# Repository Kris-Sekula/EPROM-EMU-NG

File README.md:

# EPROM-EMU-NG
EPROM Emulator Project with Arduino Nano, read more on [https://MyGeekyHobby.com](https://mygeekyhobby.com/2020/07/05/eprom-emulator/)

I have assembled devices and kits listed on [eBay](https://www.ebay.com/usr/avr4sale)

As people start building those, I encourage everyone to help creating updated firmware, software and collaborate here, report Issues if needed or contact me directly.

I get my PCBs from:

If you found this helpful and you like the work I do, why not buy me a coffe, thanks ! :)

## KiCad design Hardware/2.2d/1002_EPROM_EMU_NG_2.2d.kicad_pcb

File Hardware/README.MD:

###### Jul-9-2022

As of hardware version 1.9d and 2.2d support for a cheaper 28 pin probe has been added to the PCB, so depending on the type of probe you end up using, connector J1 has to be soldered in accordingly, see the picture below:

###### Feb-6-2022

At this point there are two differnt hardware version of the emulator, one using 2x 32kb SRAMs and the other using a single 128kb SRAM (64k usable). Firmware and software is exaclty the same for both.

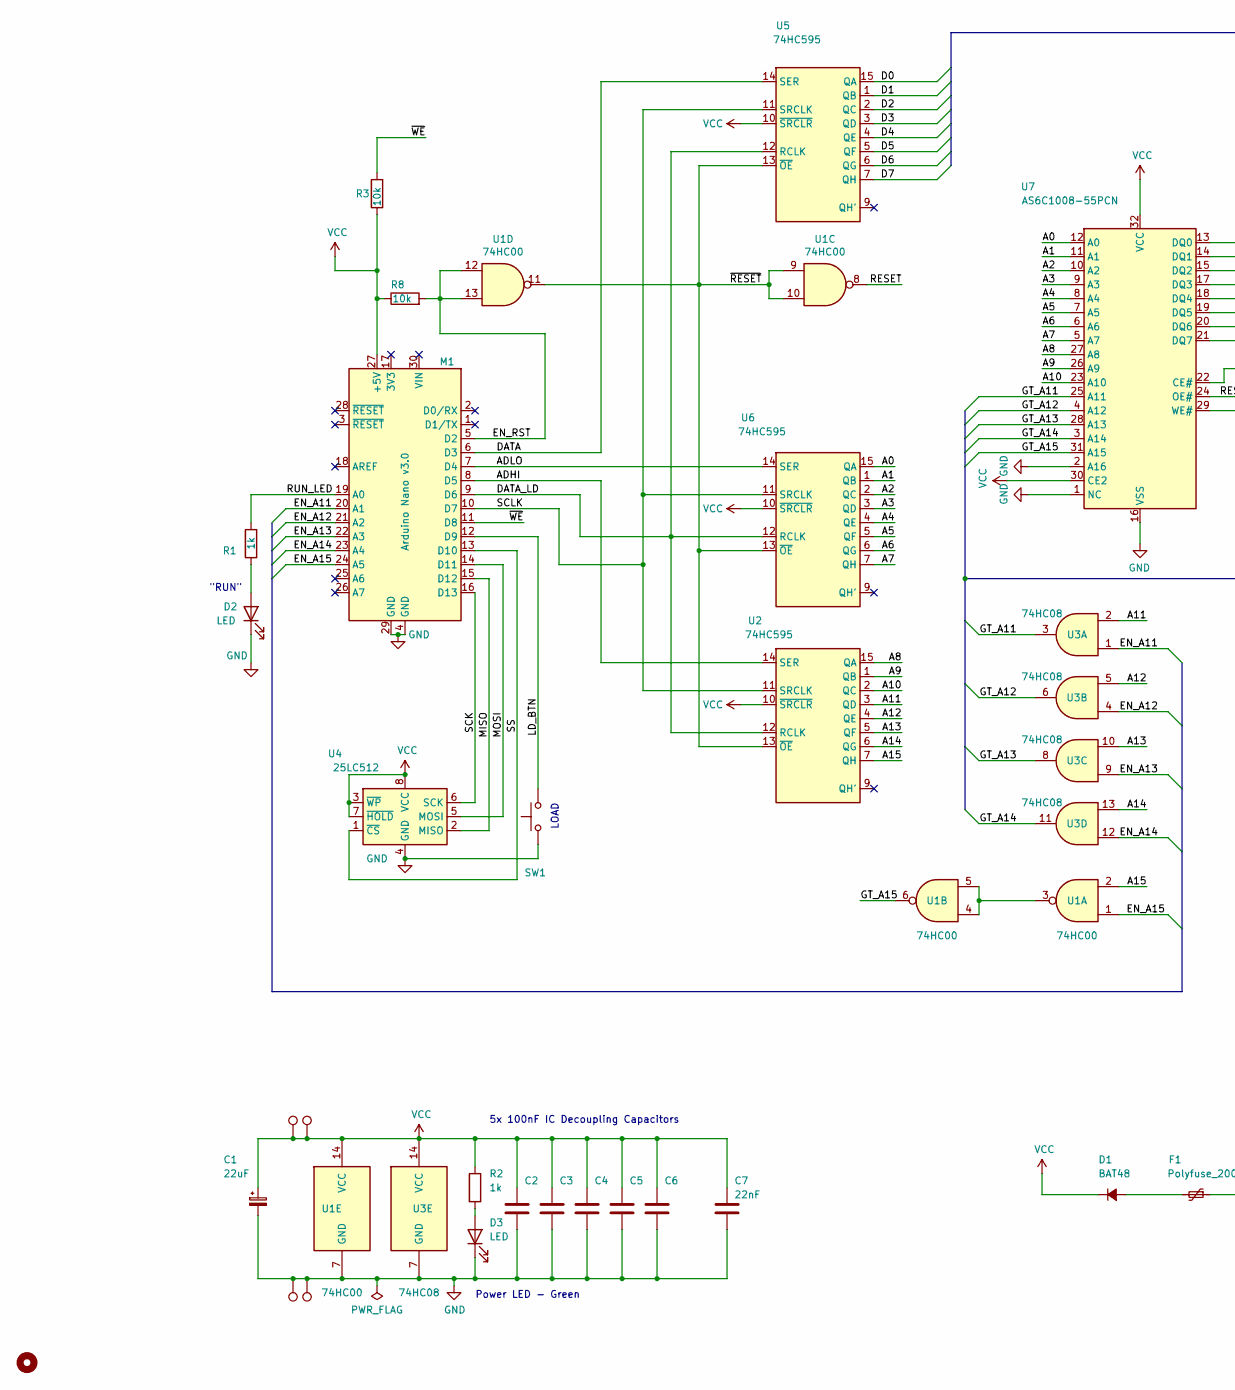
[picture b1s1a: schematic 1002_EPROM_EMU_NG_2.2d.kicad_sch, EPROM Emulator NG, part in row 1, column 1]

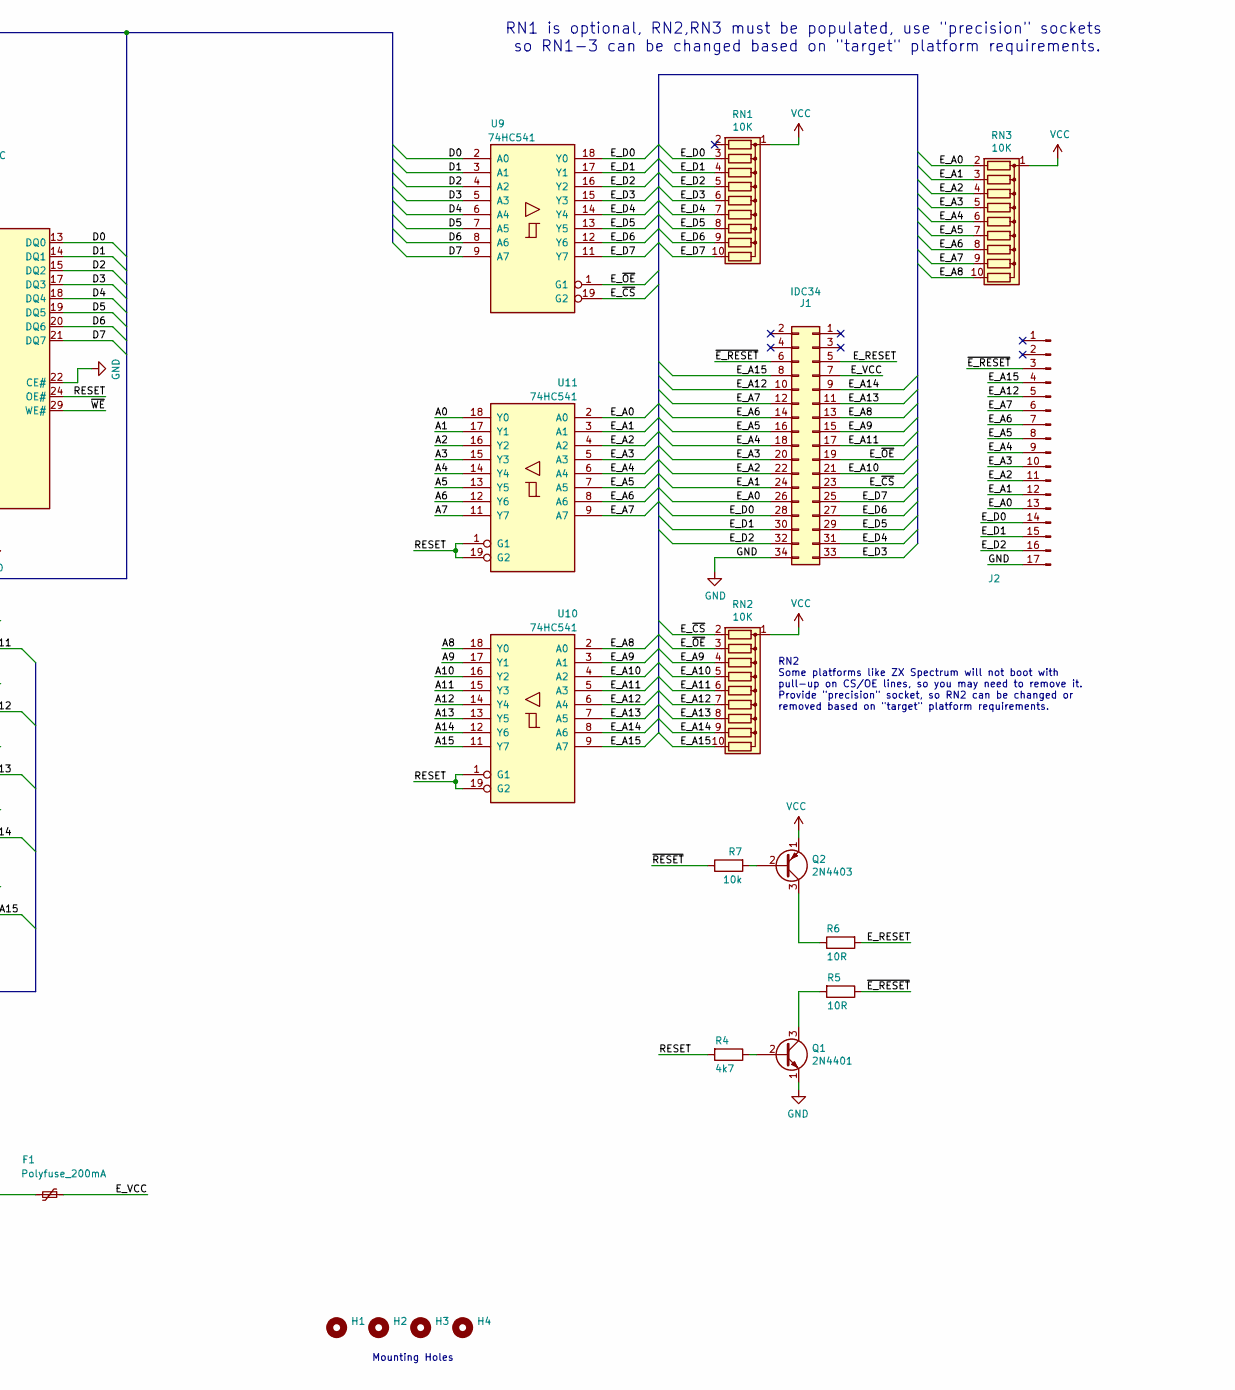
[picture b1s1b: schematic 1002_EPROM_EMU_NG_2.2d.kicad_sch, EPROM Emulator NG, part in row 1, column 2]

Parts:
C1: 22uF; CP_Radial_D6.3mm_P2.50mm
C2, C3, C4, C5, C6: 100nF; C_Disc_D4.7mm_W2.5mm_P5.00mm
C7: 22nF; C_Disc_D4.7mm_W2.5mm_P5.00mm
D1: BAT48; D_DO-35_SOD27_P7.62mm_Horizontal
D2, D3: LED; LED_D3.0mm
F1: Polyfuse_200mA; C_Disc_D10.0mm_W2.5mm_P5.00mm
H1, H2, H3, H4: MountingHole; MountingHole_2.2mm_M2
H5: MountingHole; OSHW-Logo2_9.8x8mm_SilkScreen
J1: IDC34; IDC-Header_2x17_P2.54mm_Horizontal_Lock
J2: Conn_01x17_Male; PinHeader_1x17_P2.54mm_Vertical
M1: Arduino Nano v3.0; Arduino_Nano
Q1: 2N4401; TO-92_Inline_Wide
Q2: 2N4403; TO-92_Inline_Wide
R1, R2: 1k; R_Axial_DIN0204_L3.6mm_D1.6mm_P7.62mm_Horizontal
R3, R7, R8: 10k; R_Axial_DIN0204_L3.6mm_D1.6mm_P7.62mm_Horizontal
R4: 4k7; R_Axial_DIN0204_L3.6mm_D1.6mm_P7.62mm_Horizontal
R5, R6: 10R; R_Axial_DIN0204_L3.6mm_D1.6mm_P7.62mm_Horizontal
RN1, RN2, RN3: 10K; R_Array_SIP10
SW1: SW_Push; SW_PUSH_6mm
TP1, TP4: VCC; TestPoint_THTPad_D1.5mm_Drill0.7mm
TP2, TP3: GND; TestPoint_THTPad_D1.5mm_Drill0.7mm
U1: 74HC00; DIP-14_W7.62mm_Socket
U2, U5, U6: 74HC595; DIP-16_W7.62mm_Socket
U3: 74HC08; DIP-14_W7.62mm_Socket
U4: 25LC512; DIP-8_W7.62mm_Socket
U7: AS6C1008-55PCN; DIP-32_W15.24mm_Socket
U9, U10, U11: 74HC541; DIP-20_W7.62mm_Socket

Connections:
/A0: U6.15 (QA), U7.12 (A0), U11.18 (Y0)
/A1: U6.1 (QB), U7.11 (A1), U11.17 (Y1)
/A2: U6.2 (QC), U7.10 (A2), U11.16 (Y2)
/A3: U6.3 (QD), U7.9 (A3), U11.15 (Y3)
/A4: U6.4 (QE), U7.8 (A4), U11.14 (Y4)
/A5: U6.5 (QF), U7.7 (A5), U11.13 (Y5)
/A6: U6.6 (QG), U7.6 (A6), U11.12 (Y6)
/A7: U6.7 (QH), U7.5 (A7), U11.11 (Y7)
/A8: U2.15 (QA), U7.27 (A8), U10.18 (Y0)
/A9: U2.1 (QB), U7.26 (A9), U10.17 (Y1)
/A10: U2.2 (QC), U7.23 (A10), U10.16 (Y2)
/A11: U2.3 (QD), U3.2, U10.15 (Y3)
/A12: U2.4 (QE), U3.5, U10.14 (Y4)
/A13: U2.5 (QF), U3.10, U10.13 (Y5)
/A14: U2.6 (QG), U3.13, U10.12 (Y6)
/A15: U1.2, U2.7 (QH), U10.11 (Y7)
/ADHI: M1.8 (D5), U2.14 (SER)
/ADLO: M1.7 (D4), U6.14 (SER)
/D0: U5.15 (QA), U7.13 (DQ0), U9.2 (A0)
/D1: U5.1 (QB), U7.14 (DQ1), U9.3 (A1)
/D2: U5.2 (QC), U7.15 (DQ2), U9.4 (A2)
/D3: U5.3 (QD), U7.17 (DQ3), U9.5 (A3)
/D4: U5.4 (QE), U7.18 (DQ4), U9.6 (A4)
/D5: U5.5 (QF), U7.19 (DQ5), U9.7 (A5)
/D6: U5.6 (QG), U7.20 (DQ6), U9.8 (A6)
/D7: U5.7 (QH), U7.21 (DQ7), U9.9 (A7)
/DATA: M1.6 (D3), U5.14 (SER)
/DATA_LD: M1.9 (D6), U2.12 (RCLK), U5.12 (RCLK), U6.12 (RCLK)
/EN_A11: M1.20 (A1), U3.1
/EN_A12: M1.21 (A2), U3.4
/EN_A13: M1.22 (A3), U3.9
/EN_A14: M1.23 (A4), U3.12
/EN_A15: M1.24 (A5), U1.1
/EN_RST: M1.5 (D2), R8.2, U1.12, U1.13
/E_A0: J1.26, J2.13, RN3.2 (R1), U11.2 (A0)
/E_A1: J1.24, J2.12, RN3.3 (R2), U11.3 (A1)
/E_A2: J1.22, J2.11, RN3.4 (R3), U11.4 (A2)
/E_A3: J1.20, J2.10, RN3.5 (R4), U11.5 (A3)
/E_A4: J1.18, J2.9, RN3.6 (R5), U11.6 (A4)
/E_A5: J1.16, J2.8, RN3.7 (R6), U11.7 (A5)
/E_A6: J1.14, J2.7, RN3.8 (R7), U11.8 (A6)
/E_A7: J1.12, J2.6, RN3.9 (R8), U11.9 (A7)
/E_A8: J1.13, RN3.10 (R9), U10.2 (A0)
/E_A9: J1.15, RN2.4 (R3), U10.3 (A1)
/E_A10: J1.21, RN2.5 (R4), U10.4 (A2)
/E_A11: J1.17, RN2.6 (R5), U10.5 (A3)
/E_A12: J1.10, J2.5, RN2.7 (R6), U10.6 (A4)
/E_A13: J1.11, RN2.8 (R7), U10.7 (A5)
/E_A14: J1.9, RN2.9 (R8), U10.8 (A6)
/E_A15: J1.8, J2.4, RN2.10 (R9), U10.9 (A7)
/E_D0: J1.28, J2.14, RN1.3 (R2), U9.18 (Y0)
/E_D1: J1.30, J2.15, RN1.4 (R3), U9.17 (Y1)
/E_D2: J1.32, J2.16, RN1.5 (R4), U9.16 (Y2)
/E_D3: J1.33, RN1.6 (R5), U9.15 (Y3)
/E_D4: J1.31, RN1.7 (R6), U9.14 (Y4)
/E_D5: J1.29, RN1.8 (R7), U9.13 (Y5)
/E_D6: J1.27, RN1.9 (R8), U9.12 (Y6)
/E_D7: J1.25, RN1.10 (R9), U9.11 (Y7)
/E_RESET: J1.5, R6.2
/E_VCC: F1.1, J1.7
/E_~CS: J1.23, RN2.2 (R1), U9.19 (G2)
/E_~OE: J1.19, RN2.3 (R2), U9.1 (G1)
/GT_A11: U3.3, U7.25 (A11)
/GT_A12: U3.6, U7.4 (A12)
/GT_A13: U3.8, U7.28 (A13)
/GT_A14: U3.11, U7.3 (A14)
/GT_A15: U1.6, U7.31 (A15)
/LD_BTN: M1.12 (D9), SW1.2
/MISO: M1.15 (D12), U4.2 (MISO)
/MOSI: M1.14 (D11), U4.5 (MOSI)
/RESET: R4.2, U1.8, U7.24 (OE#), U10.1 (G1), U10.19 (G2), U11.1 (G1), U11.19 (G2)
/RUN_LED: M1.19 (A0), R1.2
/SCK: M1.16 (D13), U4.6 (SCK)
/SCLK: M1.10 (D7), U2.11 (SRCLK), U5.11 (SRCLK), U6.11 (SRCLK)
/SS: M1.13 (D10), U4.1 (~CS)
/~E_RESET: J1.6, J2.3, R5.1
/~RESET: R7.1, U1.9, U1.10, U1.11, U2.13 (~OE), U5.13 (~OE), U6.13 (~OE)
/~WE: M1.11 (D8), R3.2, U7.29 (WE#)
GND: C1.2, C2.2, C3.2, C4.2, C5.2, C6.2, C7.2, D2.1 (K), D3.1 (K), J1.34, J2.17, M1.4 (GND), M1.29 (GND), Q1.1 (E), SW1.1, TP2.1, TP3.1, U1.7 (GND), U2.8 (GND), U3.7 (GND), U4.4 (GND), U5.8 (GND), U6.8 (GND), U7.1 (NC), U7.2 (A16), U7.16 (VSS), U7.22 (CE#), U9.10 (GND), U10.10 (GND), U11.10 (GND)
unnamed: D1.2 (A), F1.2
unnamed: D2.2 (A), R1.1
unnamed: D3.2 (A), R2.2
unnamed: Q1.2 (B), R4.1
unnamed: Q1.3 (C), R5.2
unnamed: Q2.2 (B), R7.2
unnamed: Q2.3 (C), R6.1
unnamed: U1.3, U1.4, U1.5
VCC: C1.1, C2.1, C3.1, C4.1, C5.1, C6.1, C7.1, D1.1 (K), M1.27 (+5V), Q2.1 (E), R2.1, R3.1, R8.1, RN1.1 (common), RN2.1 (common), RN3.1 (common), TP1.1, TP4.1, U1.14 (VCC), U2.10 (~SRCLR), U2.16 (VCC), U3.14 (VCC), U4.3 (~WP), U4.7 (~HOLD), U4.8 (VCC), U5.10 (~SRCLR), U5.16 (VCC), U6.10 (~SRCLR), U6.16 (VCC), U7.30 (CE2), U7.32 (VCC), U9.20 (VCC), U10.20 (VCC), U11.20 (VCC)

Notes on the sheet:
RN2 Some platforms like ZX Spectrum will not boot with pull-up on CS/OE lines, so you may need to remove it. Provide "precision" socket, so RN2 can be changed or removed based on "target" platform requirements.
"RUN"
Power LED - Green
LOAD
RN1 is optional, RN2,RN3 must be populated, use "precision" sockets so RN1-3 can be changed based on "target" platform requirements.
5x 100nF IC Decoupling Capacitors
Mounting Holes

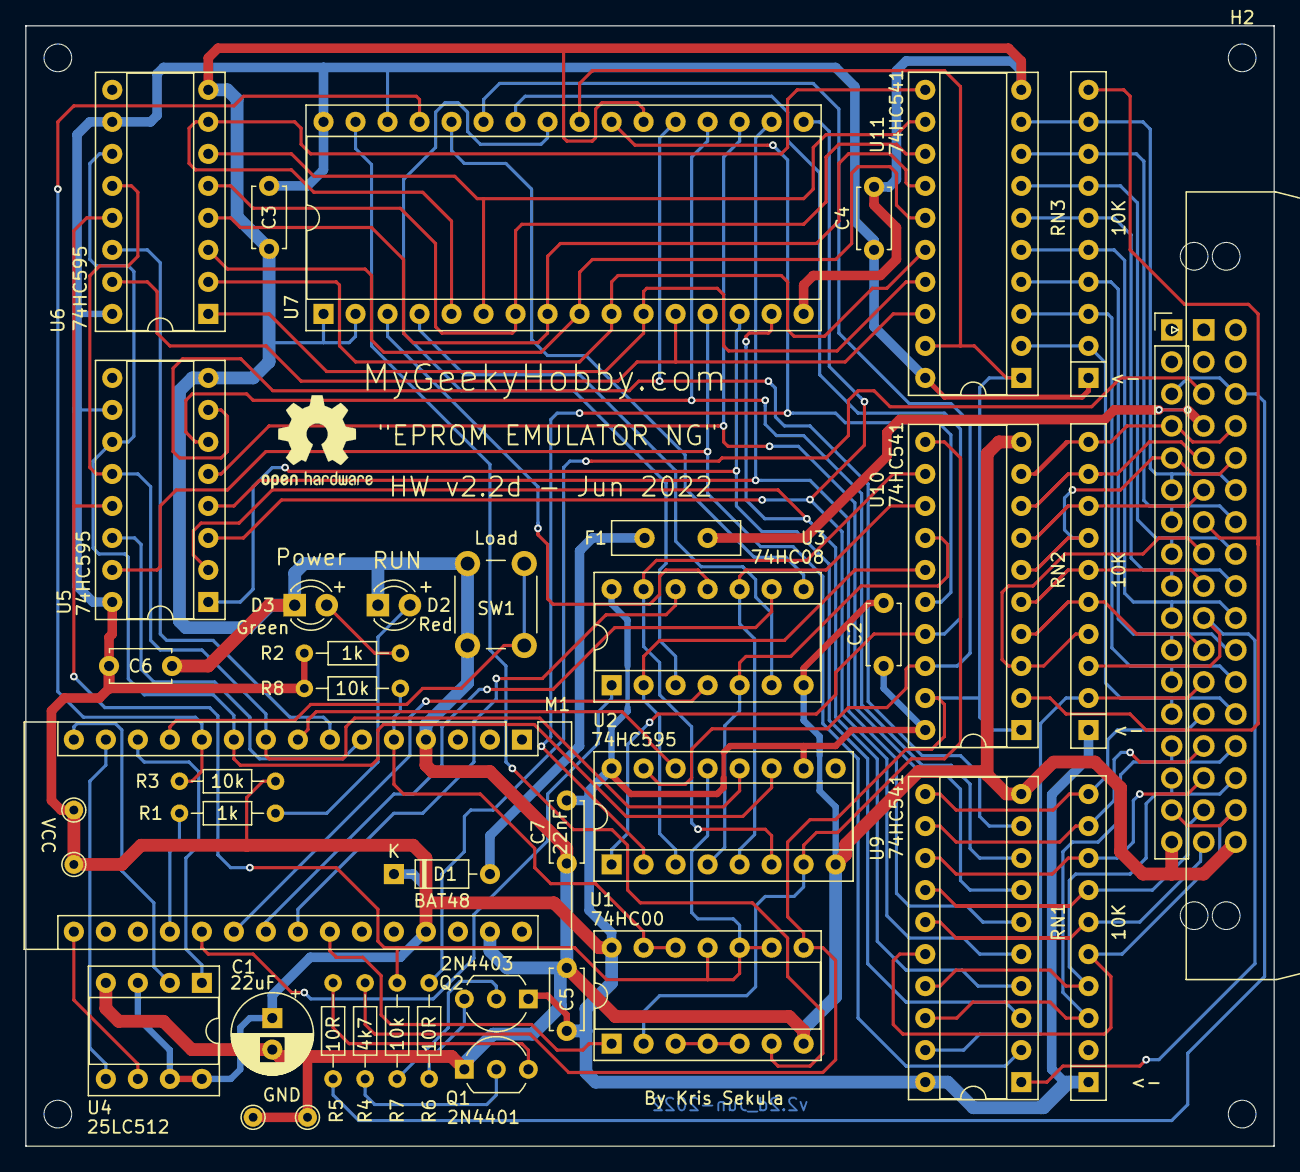
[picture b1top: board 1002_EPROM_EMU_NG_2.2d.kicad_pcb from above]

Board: 2 copper layers, 99.1 x 88.9 mm, 47 parts (0 on the bottom side), 88 nets.

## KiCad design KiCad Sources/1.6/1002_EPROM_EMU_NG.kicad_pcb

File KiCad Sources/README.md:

KiCad project files.

Version 2.2: Reshuffled component designations for pcb v1.9c and 2.2c to keep them in sync - help to keep the BoM alligned... only delta is the SRAM

Version 2.1: Moved from using 2x 32k SRAM to single 128k SRAM (64k usable). Firware and software is the same for both.

Version 1.9: Added pull-up resistors to /WE and EN_RST, helps prevent SRAM corruption during Arduino reset (needed only when doing partial uploads)

Version 1.8b: Fixed the footprint for Q1-2N4401 and Q2-2N4403, see Errata document for more details.

Version 1.8: I re-shuffled resistor networks, added RN3 to offer optional pull-up resistors for address line A0-A7, RN2 should be populated, RN1 and RN3 are optional. Added Q3 for my experiments, but there is no need to populate that transistor.

Version 1.7: Minor fix for a desing flaw as described in the ERRATA document. I also enlarged the holes for J1 as depeding on vendor of the connector in some cases the fit was very tight.

Version 1.6: Added some component description on silkscreen, no changes to tracks routing.

Version 1.4: I re-routed the power and improved the PCB design.

Version 1.0: After I built the first 5 prototypes, I discovered an issue with the PCB layout, one of the shift registers (U11) was getting onto a CMOS latch-up state, even though I had a few bypass caps around the PCB, I was still occasionally getting the issues. I fixed the prototypes by "bodging" a few connections at the bottom of the pcb.

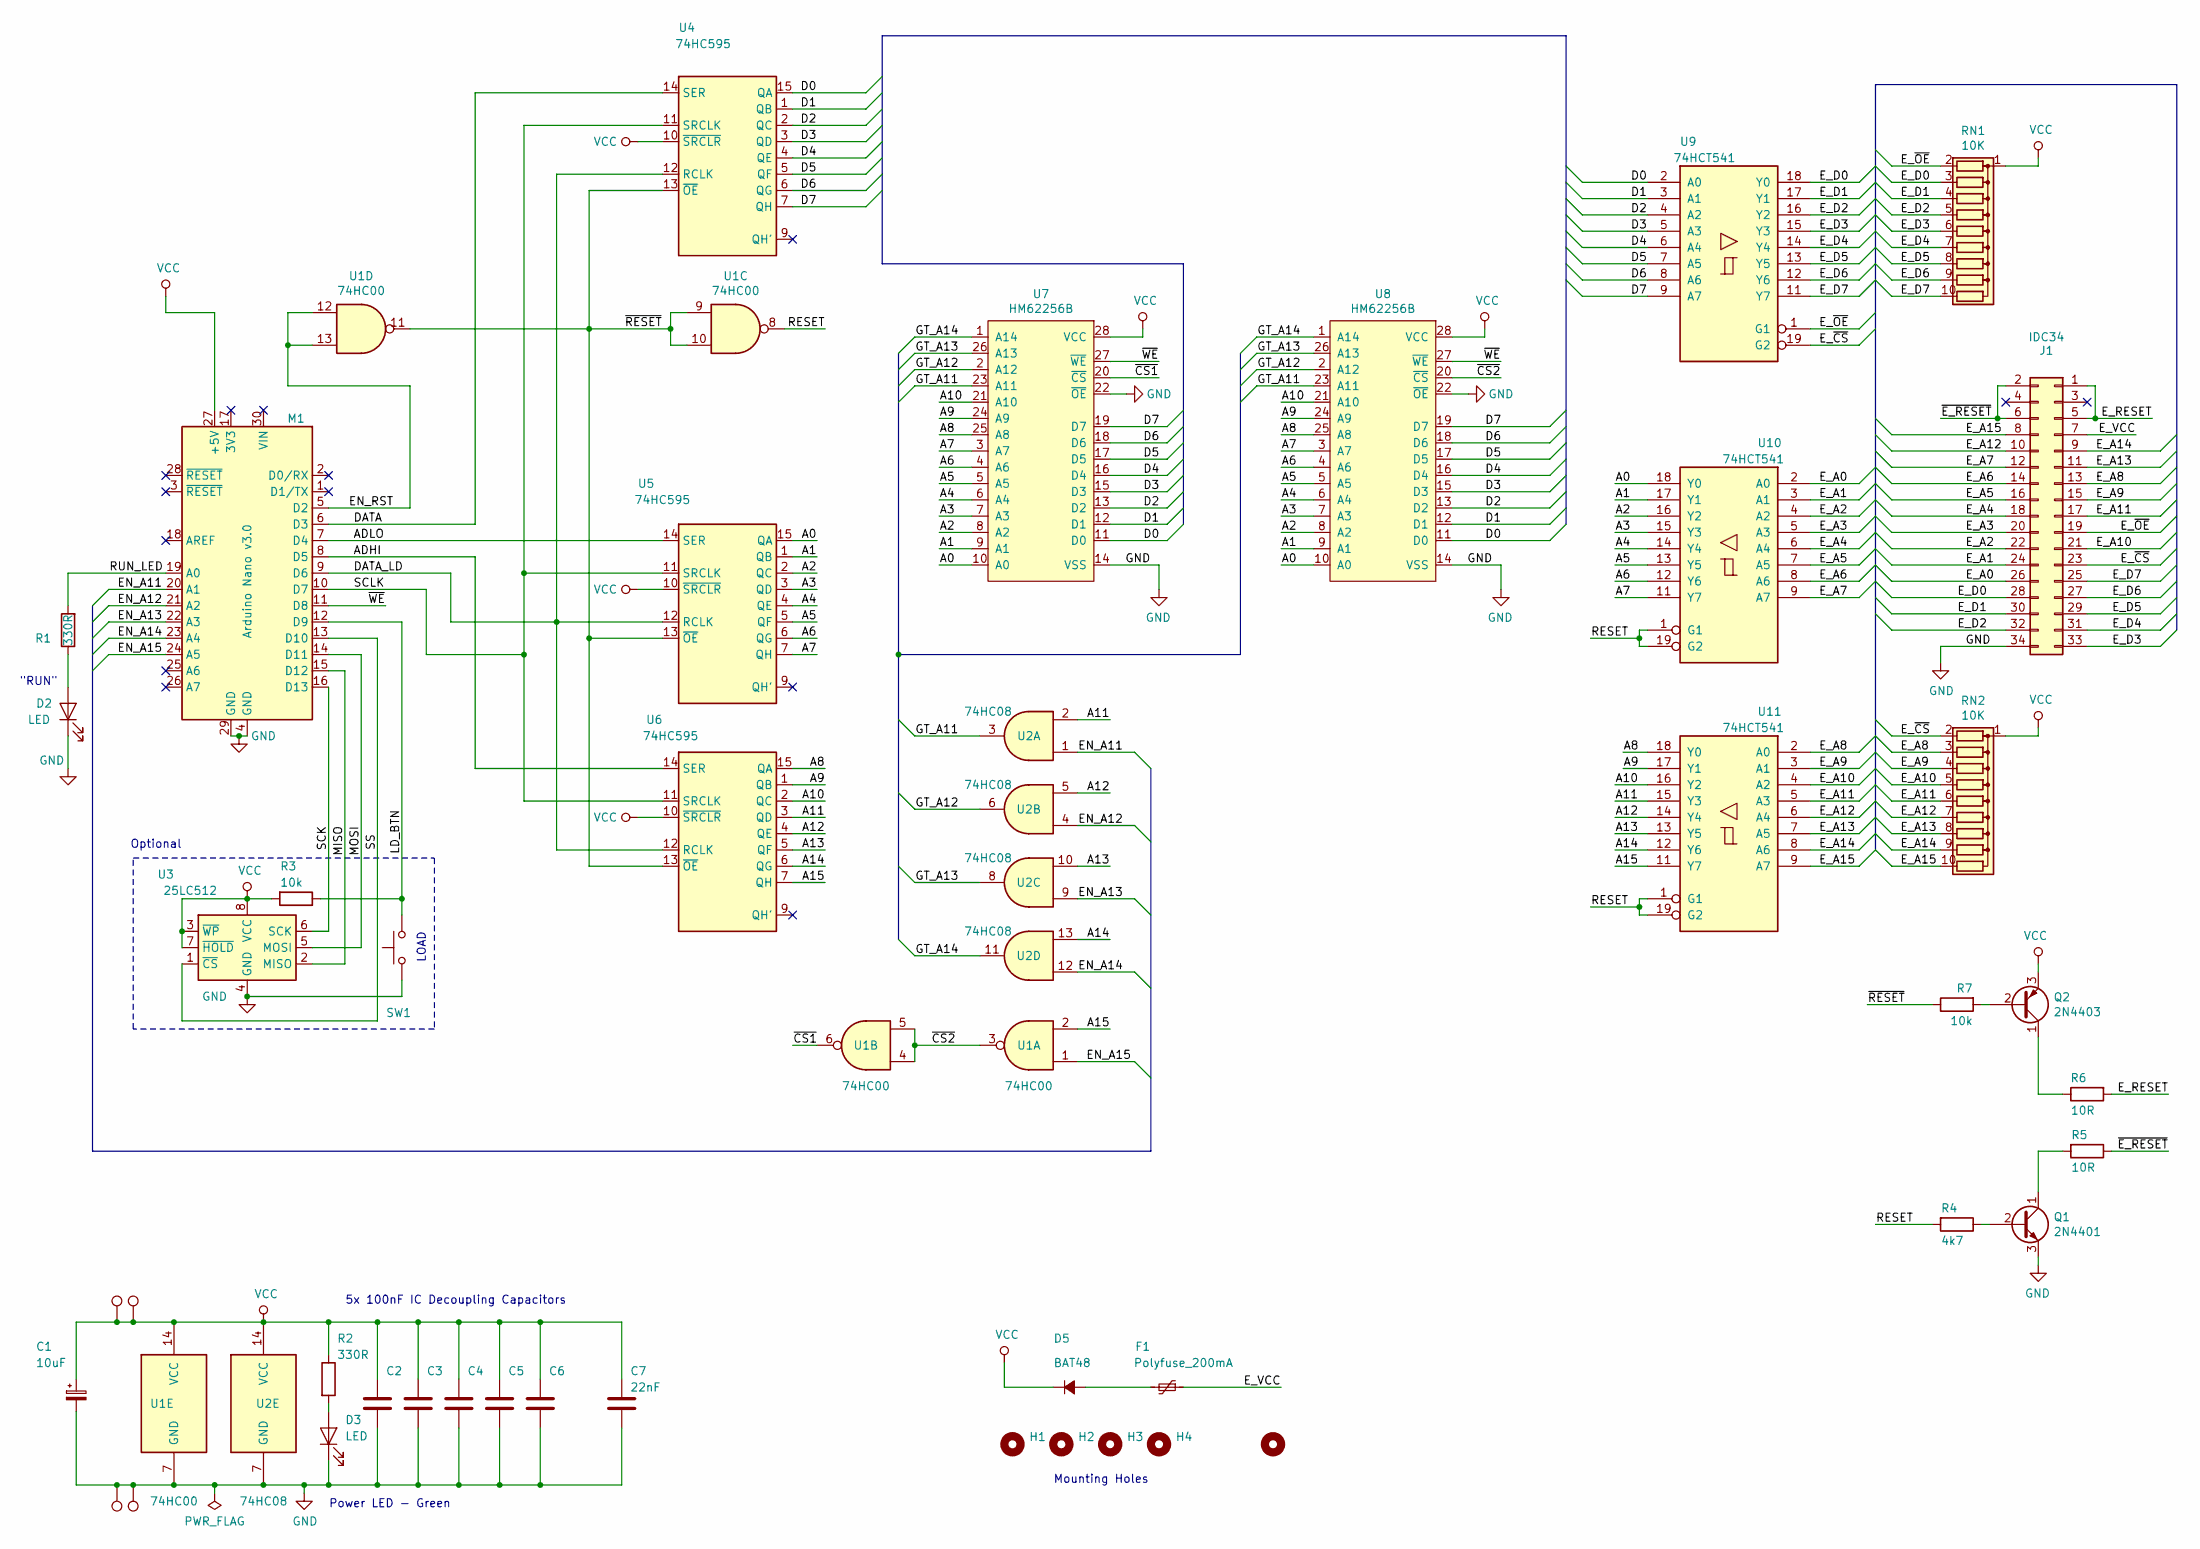
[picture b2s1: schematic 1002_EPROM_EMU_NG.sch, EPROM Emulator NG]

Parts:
C1: 10uF; CP_Radial_D6.3mm_P2.50mm
C2, C3, C4, C5, C6: 100nF; C_Disc_D4.7mm_W2.5mm_P5.00mm
C7: 22nF; C_Disc_D4.7mm_W2.5mm_P5.00mm
D2, D3: LED; LED_D3.0mm
D5: BAT48; D_DO-35_SOD27_P7.62mm_Horizontal
F1: Polyfuse_200mA; C_Disc_D10.0mm_W2.5mm_P5.00mm
H1, H2, H3, H4: MountingHole; MountingHole_2.2mm_M2
H5: MountingHole; OSHW-Logo2_9.8x8mm_SilkScreen
J1: IDC34; IDC-Header_2x17_P2.54mm_Horizontal_Lock
M1: Arduino Nano v3.0; Arduino_Nano
Q1: 2N4401; TO-92_Inline_Wide
Q2: 2N4403; TO-92_Inline_Wide
R1, R2: 330R; R_Axial_DIN0204_L3.6mm_D1.6mm_P7.62mm_Horizontal
R3, R7: 10k; R_Axial_DIN0204_L3.6mm_D1.6mm_P7.62mm_Horizontal
R4: 4k7; R_Axial_DIN0204_L3.6mm_D1.6mm_P7.62mm_Horizontal
R5, R6: 10R; R_Axial_DIN0204_L3.6mm_D1.6mm_P7.62mm_Horizontal
RN1, RN2: 10K; R_Array_SIP10
SW1: SW_Push; SW_PUSH_6mm
TP1, TP4: VCC; TestPoint_THTPad_D1.5mm_Drill0.7mm
TP2, TP3: GND; TestPoint_THTPad_D1.5mm_Drill0.7mm
U1: 74HC00; DIP-14_W7.62mm_Socket
U2: 74HC08; DIP-14_W7.62mm_Socket
U3: 25LC512; DIP-8_W7.62mm_Socket
U4, U5, U6: 74HC595; DIP-16_W7.62mm_Socket
U7, U8: HM62256B; DIP-28_W15.24mm_Socket
U9, U10, U11: 74HCT541; DIP-20_W7.62mm_Socket

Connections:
/A0: U5.15 (QA), U7.10 (A0), U8.10 (A0), U10.18 (Y0)
/A1: U5.1 (QB), U7.9 (A1), U8.9 (A1), U10.17 (Y1)
/A2: U5.2 (QC), U7.8 (A2), U8.8 (A2), U10.16 (Y2)
/A3: U5.3 (QD), U7.7 (A3), U8.7 (A3), U10.15 (Y3)
/A4: U5.4 (QE), U7.6 (A4), U8.6 (A4), U10.14 (Y4)
/A5: U5.5 (QF), U7.5 (A5), U8.5 (A5), U10.13 (Y5)
/A6: U5.6 (QG), U7.4 (A6), U8.4 (A6), U10.12 (Y6)
/A7: U5.7 (QH), U7.3 (A7), U8.3 (A7), U10.11 (Y7)
/A8: U6.15 (QA), U7.25 (A8), U8.25 (A8), U11.18 (Y0)
/A9: U6.1 (QB), U7.24 (A9), U8.24 (A9), U11.17 (Y1)
/A10: U6.2 (QC), U7.21 (A10), U8.21 (A10), U11.16 (Y2)
/A11: U2.2, U6.3 (QD), U11.15 (Y3)
/A12: U2.5, U6.4 (QE), U11.14 (Y4)
/A13: U2.10, U6.5 (QF), U11.13 (Y5)
/A14: U2.13, U6.6 (QG), U11.12 (Y6)
/A15: U1.2, U6.7 (QH), U11.11 (Y7)
/ADHI: M1.8 (D5), U6.14 (SER)
/ADLO: M1.7 (D4), U5.14 (SER)
/D0: U4.15 (QA), U7.11 (D0), U8.11 (D0), U9.2 (A0)
/D1: U4.1 (QB), U7.12 (D1), U8.12 (D1), U9.3 (A1)
/D2: U4.2 (QC), U7.13 (D2), U8.13 (D2), U9.4 (A2)
/D3: U4.3 (QD), U7.15 (D3), U8.15 (D3), U9.5 (A3)
/D4: U4.4 (QE), U7.16 (D4), U8.16 (D4), U9.6 (A4)
/D5: U4.5 (QF), U7.17 (D5), U8.17 (D5), U9.7 (A5)
/D6: U4.6 (QG), U7.18 (D6), U8.18 (D6), U9.8 (A6)
/D7: U4.7 (QH), U7.19 (D7), U8.19 (D7), U9.9 (A7)
/DATA: M1.6 (D3), U4.14 (SER)
/DATA_LD: M1.9 (D6), U4.12 (RCLK), U5.12 (RCLK), U6.12 (RCLK)
/EN_A11: M1.20 (A1), U2.1
/EN_A12: M1.21 (A2), U2.4
/EN_A13: M1.22 (A3), U2.9
/EN_A14: M1.23 (A4), U2.12
/EN_A15: M1.24 (A5), U1.1
/EN_RST: M1.5 (D2), U1.12, U1.13
/E_A0: J1.26, U10.2 (A0)
/E_A1: J1.24, U10.3 (A1)
/E_A2: J1.22, U10.4 (A2)
/E_A3: J1.20, U10.5 (A3)
/E_A4: J1.18, U10.6 (A4)
/E_A5: J1.16, U10.7 (A5)
/E_A6: J1.14, U10.8 (A6)
/E_A7: J1.12, U10.9 (A7)
/E_A8: J1.13, RN2.3 (R2), U11.2 (A0)
/E_A9: J1.15, RN2.4 (R3), U11.3 (A1)
/E_A10: J1.21, RN2.5 (R4), U11.4 (A2)
/E_A11: J1.17, RN2.6 (R5), U11.5 (A3)
/E_A12: J1.10, RN2.7 (R6), U11.6 (A4)
/E_A13: J1.11, RN2.8 (R7), U11.7 (A5)
/E_A14: J1.9, RN2.9 (R8), U11.8 (A6)
/E_A15: J1.8, RN2.10 (R9), U11.9 (A7)
/E_D0: J1.28, RN1.3 (R2), U9.18 (Y0)
/E_D1: J1.30, RN1.4 (R3), U9.17 (Y1)
/E_D2: J1.32, RN1.5 (R4), U9.16 (Y2)
/E_D3: J1.33, RN1.6 (R5), U9.15 (Y3)
/E_D4: J1.31, RN1.7 (R6), U9.14 (Y4)
/E_D5: J1.29, RN1.8 (R7), U9.13 (Y5)
/E_D6: J1.27, RN1.9 (R8), U9.12 (Y6)
/E_D7: J1.25, RN1.10 (R9), U9.11 (Y7)
/E_RESET: J1.1, J1.5, R6.2
/E_VCC: F1.1, J1.7
/E_~CS~: J1.23, RN2.2 (R1), U9.19 (G2)
/E_~OE~: J1.19, RN1.2 (R1), U9.1 (G1)
/GT_A11: U2.3, U7.23 (A11), U8.23 (A11)
/GT_A12: U2.6, U7.2 (A12), U8.2 (A12)
/GT_A13: U2.8, U7.26 (A13), U8.26 (A13)
/GT_A14: U2.11, U7.1 (A14), U8.1 (A14)
/LD_BTN: M1.12 (D9), R3.1, SW1.2
/MISO: M1.15 (D12), U3.2 (MISO)
/MOSI: M1.14 (D11), U3.5 (MOSI)
/RESET: R4.2, U1.8, U10.1 (G1), U10.19 (G2), U11.1 (G1), U11.19 (G2)
/RUN_LED: M1.19 (A0), R1.2
/SCK: M1.16 (D13), U3.6 (SCK)
/SCLK: M1.10 (D7), U4.11 (SRCLK), U5.11 (SRCLK), U6.11 (SRCLK)
/SS: M1.13 (D10), U3.1 (~CS)
/~CS1~: U1.6, U7.20 (~CS)
/~CS2~: U1.3, U1.4, U1.5, U8.20 (~CS)
/~E_RESET~: J1.2, J1.6, R5.1
/~RESET~: R7.1, U1.9, U1.10, U1.11, U4.13 (~OE), U5.13 (~OE), U6.13 (~OE)
/~WE~: M1.11 (D8), U7.27 (~WE), U8.27 (~WE)
GND: C1.2, C2.2, C3.2, C4.2, C5.2, C6.2, C7.2, D2.1 (K), D3.1 (K), J1.34, M1.4 (GND), M1.29 (GND), Q1.3 (E), SW1.1, TP2.1, TP3.1, U1.7 (GND), U2.7 (GND), U3.4 (GND), U4.8 (GND), U5.8 (GND), U6.8 (GND), U7.14 (VSS), U7.22 (~OE), U8.14 (VSS), U8.22 (~OE), U9.10 (GND), U10.10 (GND), U11.10 (GND)
unnamed: D2.2 (A), R1.1
unnamed: D3.2 (A), R2.2
unnamed: D5.2 (A), F1.2
unnamed: Q1.1 (C), R5.2
unnamed: Q1.2 (B), R4.1
unnamed: Q2.1 (C), R6.1
unnamed: Q2.2 (B), R7.2
VCC: C1.1, C2.1, C3.1, C4.1, C5.1, C6.1, C7.1, D5.1 (K), M1.27 (+5V), Q2.3 (E), R2.1, R3.2, RN1.1 (common), RN2.1 (common), TP1.1, TP4.1, U1.14 (VCC), U2.14 (VCC), U3.3 (~WP), U3.7 (~HOLD), U3.8 (VCC), U4.10 (~SRCLR), U4.16 (VCC), U5.10 (~SRCLR), U5.16 (VCC), U6.10 (~SRCLR), U6.16 (VCC), U7.28 (VCC), U8.28 (VCC), U9.20 (VCC), U10.20 (VCC), U11.20 (VCC)

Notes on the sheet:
5x 100nF IC Decoupling Capacitors
Power LED - Green
"RUN"
LOAD
Optional
Mounting Holes

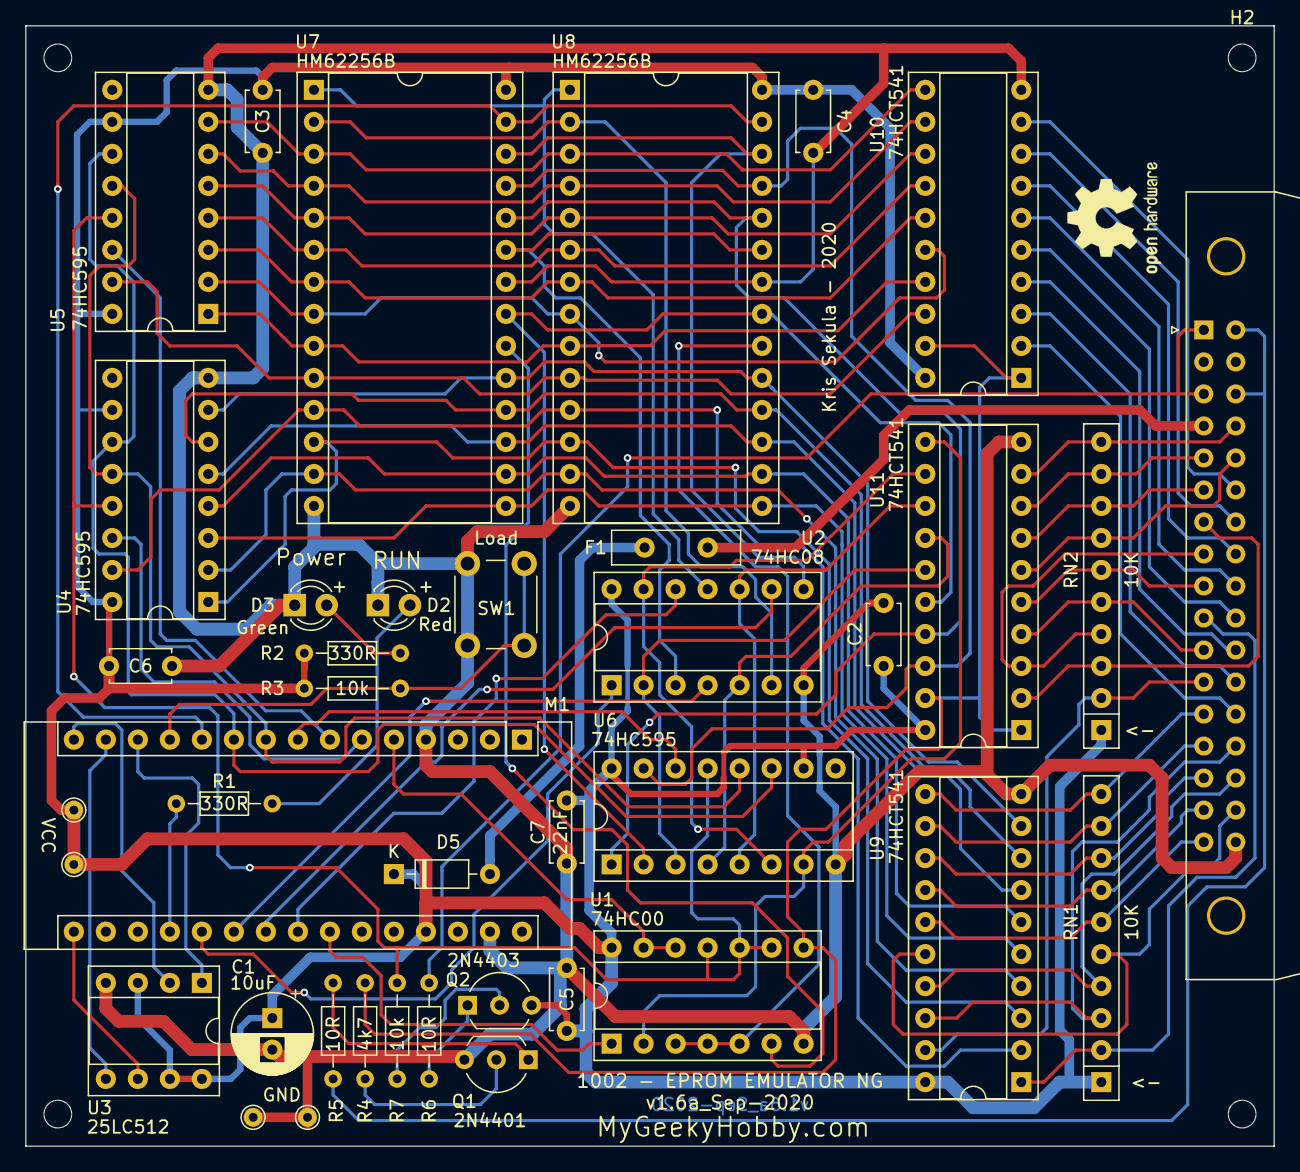
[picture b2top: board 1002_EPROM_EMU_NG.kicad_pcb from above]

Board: 2 copper layers, 99.1 x 88.9 mm, 45 parts (0 on the bottom side), 88 nets.

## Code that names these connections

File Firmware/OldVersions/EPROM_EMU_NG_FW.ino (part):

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#include <EEPROM.h>

#define DATA 3  // data pin for shift register handling D0-D7
#define ADLO 4  // data pin for shift register handling A0-A7
#define ADHI 5  // data pin for shift register handling A8-A15
#define SCLK 7  // clock ping for all shift registers

#define DAT_LD 6  // latch pin for all shift registers 


#define EN_RST 2  //  internal / external bus control pin
#define WE 8      // SRAM Write Enable Pin

#define LD_BTN 9  // load data from SPI button
#define LED_G A0  // RED LED 

// Gating signals - ignores selected A11 - A15 address pins besed on EPROM Type
#define EN_A11 A1  // A11 data pin gating signal 
#define EN_A12 A2  // A12 data pin gating signal 
#define EN_A13 A3  // A13 data pin gating signal 
#define EN_A14 A4  // A14 data pin gating signal 
#define EN_A15 A5  // A15 data pin gating signal 

// SPI EEPROM stuff

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//

void setup() {
  pinMode( EN_RST, OUTPUT ); digitalWrite( EN_RST, HIGH );  // disable outputs to start with AD0-15 from outside

  pinMode( DATA, OUTPUT ); digitalWrite( DATA, LOW );
  pinMode( ADLO, OUTPUT ); digitalWrite( ADLO, LOW );
  pinMode( ADHI, OUTPUT ); digitalWrite( ADHI, LOW );

  pinMode( DAT_LD, OUTPUT ); digitalWrite( DAT_LD, LOW );
  pinMode( SCLK, OUTPUT ); digitalWrite( SCLK, LOW );
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  pinMode( LED_G, OUTPUT ); digitalWrite( LED_G, LOW );

  // address lines gate signals as outputs
  pinMode( EN_A11, OUTPUT );
  pinMode( EN_A12, OUTPUT );
  pinMode( EN_A13, OUTPUT ); 
  pinMode( EN_A14, OUTPUT );
  pinMode( EN_A15, OUTPUT );
  
  setBus(6); //  default settings to enable all address lines  6 = 27512 memory code

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
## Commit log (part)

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2020-06-22 Create Firmware Foder
2020-06-22 Initial version
    Version control via github starts from here
2020-06-22 Create Software folder
2020-06-22 Initial upload
    version control via GitHub starts here
2020-06-22 Rename EPROM_EMU_NG_FW_v2_w_SPI.ino to EPROM_EMU_NG_FW.ino
2020-06-23 3d-Case Folder added
2020-06-23 STL for base added
2020-06-23 Rename Readme.txt to README.md
2020-07-06 Added a few fixes to create the 1.4 version of PCB
    Pull up on CE on OE added
2020-07-06 Version 1.4 of PCB, with optimised power routing.
    Hopefully this will fix the CMOS latch-up I was getting on U11
2020-07-06 pull ups added
2020-07-06 Delete 1002_EPROM_EMU_NG_pcb_3D.png
    to be replaced by 1.4 pcb
2020-07-08 Update EPROM_EMU_NG_FW.ino
    Updated link to the page
2020-07-12 Added Digikey based BOM
    Don't buy the Arduino Nano in Digikey, use Amazon or eBay instead as it's much cheaper there. I added it to the DigiKey BOM for completeness.
2020-07-16 Fixed a potential bug when Saving to SPI EEPROM
2020-07-16 Bug fix for SPI EEPROM save
    potentially fixed a bug with SPI EEPROM save
2020-07-16 Minor changes
    Removed scrolling of address while loading
2020-07-23 Create LICENSE
2020-07-23 Create NOTICE
2020-09-29 Adds a GUI based parameter selection !!! BETA !!!
    # ver 1.6g - Aug 2020 - Lunches GUI when no parameters specified (code contributed by John Gerrard)... requires PySimpleGUI module "pip install PySimpleGUI"
    It's a "beta" version, so test and let me know if it works for you.
2020-10-03 Fixed bug in GUI version
2020-10-03 Adds a GUI based parameter selection !!! BETA !!!
2020-10-06 updated BOM to version 1.6, added SIP socket for RNs and adjusted some parts to better fit the PCB
2020-10-06 clean up old BOM
2020-10-06 Added csv BOM
2020-10-07 Updated PCB to version 1.6
2020-10-07 Added picture of v1.5 PCB
2020-10-09 Added Brother laber printer formatted label for the DIP28 emulator probe, also a png version for standard printer.
2020-10-26 Add files via upload
    v1.7 PCB, DON'T USE YET
2020-10-26 Do NOT use 1.7 yet, not confirmed working yet.
2020-10-27 Added Errata file for PCB 1.6 and below
    A recommended fix for a design flaw in PCB versions 1.6 and below.
2020-10-27 Use this firmware with PCB ver 1.6 or lower
    See the Errata pdf for details, Option B - beta firmware fix for the emulator if you are unable to perform the HW modification.
2020-10-28 1.7b not officially released yet
    Has the fix for /OE ... changed all ICs to be HC, but some targets may require HCT for the 541 buffers.
2020-10-28 includes the fix for /OE to SRAM
    waiting for PCBs before I officially release this version
2020-11-09 Added 2.0rc1
    Release Candidate 1 for firmware 2.0
    * Uses binary transfer mode
    * SPI EEPROM save option works across entire 64k address space
2020-11-09 Adde Python script 2.0rc1 and release notes
    This is release candidate 1 for software version 2.0
    * save parameters in GUI
    * .bin and .hex file support
    * binary mode upload with packets of 128-512 bytes at a time
    * Save to SPI works with any type of data range (any source file less than 128 bytes gets "padded" with 0xFF)
2020-11-14 Added DIP24 probe design
2020-11-14 DIP24 Probe pictures
2020-11-19 1.8b
    Added version 1.8b of the PCB. Includes fixes to the SRAM CS line as well as the silkscreen for Q1(2N4401) and Q2(2N4403)
2020-11-19 Updated Errata Files
2020-11-19 Fixed Q1 and Q2 footprint
2020-11-19 upadated version number to 1.8b in schematic
2020-11-19 Reshuffled files into folders
2020-11-19 Updated KiCad Sources
2020-11-19 updated Probe Design document
2020-11-23 Added 2.0rc2
    Fixes major bug where chunks of "00h" data were treated as "no data".
2020-11-23 missed some code in RC2 from RC1 ... fixed now
2020-12-23 Code cleanup, SPI to SRAM load speed improvements
    Major code cleanup, thanks to Hubert H. Long press of the LOAD button does a 150ms target reset (if you connect the reset hook to your target)
2021-01-17 1.9 KiCad sources uploaded
2021-01-17 Uploaded HW v2.1 KiCad sources
2021-04-10 Updated files to version 2.2
    Cosmetic changes to schematic and PCB
2021-04-10 HW-2.1 picture added
2021-04-10 Updated main picture to hw 2.1
2021-04-11 FW 2.0rc8 with EEPROM Support
2021-04-11 Added support for EEPROM
2021-04-12 Added FW version rc9
2021-04-12 Python code 2.0rc9 added
    Fixed transfer size to 1024 bytes as 2048 was causing issues on macOS
2021-04-12 Delete EPROM_EMU_NG_FW_2.0rc8.ino
    doesn't work with macOS
2021-04-25 Added assembly instructions for HW 2.2
2021-08-22 fix for black nano v3 causing issues
    Black Nano v3 clones with vqfn atmage328p were misbehaving, this small fix seems to make things work again
2021-10-11 1.9c assembly instructions and Gerbers added
2021-10-11 Schematic diagram for 1.9c added
2021-10-11 2.2c BOM, gerbers and schematic diagram added
2021-10-11 2.2c assembly instruction added
2021-10-11 1.9c added Digikey compatible BoM
2021-11-15 Added few fixes submitted by Ralf
    Fixed bugs related to EEPROM memory type
2021-11-15 Added few fixes submitted by Ralf
    corrected fw ver string
2021-12-13 Added KiCad Sources for 2.2c
2021-12-26 added workarounds for ATMEGA328PB as found in some new Nano clones
2021-12-26 Cleanup of old files
2021-12-26 reshuffle folders
2021-12-26 reshuffle files
2021-12-26 Added Nano_328PB picture with modded Reset circuit
2022-01-18 updated BOMs
2022-07-10 Added support for TLY 3100 DIP 28 probe
2022-07-10 Support for TLY 3100 dip 28 probe added
2023-08-27 Adding a timeout wait for initial HW prompt. Previously, the script could fail when the Autoload feature was enabled for larger ROM sizes.
2023-10-10 Added 2.2d KiCad sources
2023-10-10 Delete Hardware/2.2d/1002_EPROM_EMU_NG_2.2d.pdf
    updating pdfs
2023-10-10 updated schematic pdf
2023-12-31 updated instructions to 2.2c(B)
2023-12-31 updated assembly instructions to ver.2.2c(B)
2024-01-31 updated BOM
2024-01-31 Delete Hardware/2.2d/EpromEmu_2_2d_BoM_DigiKey_v1.xlsx
    updated to v2
2024-04-17 Added a CLI-only version of the python code
    For testing on machines where it's hard to install the GUI library
2025-01-03 Update UI
2025-01-04 updated README files
2025-01-05 Fix indentation
    Some code was indented with spaces instead of tabs, which is
    overwhelminly used in the rest of the code. Unify.
2025-01-05 Fallback for saved window position
    when using the emulator from different devices with different screen
    resolutions, the saved position might not be valid. If that is the
    case, use a default location.
2025-01-05 Switch communication to be all in binary
    Instead of encoding/decoding all serial communication to the terminal's
    encoding, keep everything in binary for communications and decode only
    when printing to the terminal.
    This solves my issue where the script crashed when running on a raspberry
    pi through ssh from a macOS machine.
2025-01-05 Make output of the script more compact
    Make it easier to parse script output at a glance:
    $ epromemung -mem 27512 -spi y -auto y a4091_cdfs.rom /dev/ttyUSB1
    EPROM EMU NG tool v2.0rc10
    Processing a4091_cdfs.rom... done (bin)
    Using serial port /dev/ttyUSB1, emulating: 27512 EPROM
    <- attempting to get sync
2025-01-05 Simplify Intel line parsing
2025-01-05 Verify that file loaded is not larger than buffer
2025-03-07 Update README.MD
    updated PySimpleGui instructions
2025-03-07 Update PySimpleGui instructions.
2025-03-26 added a pyqt5 version of the GUI app
2025-03-26 Update EPROM_NG_V2.0rc3.pyqt5.py
    Added PyQT5 version of script - thanks Joe!
2025-03-26 Added PyQt5 version of code - thanks Joe!
    needs PyQt5 installed: pip install PyQt5
2025-03-31 Add EPROM_NG_v2.0rc4.py - move to using FreeSimpleGUI, only load gui library if needed, show friendly import errors
2025-03-31 Update README.MD
    Re-organize
2025-03-31 Added GUI Picture
2025-08-21 Update README.md
    adjusted url
